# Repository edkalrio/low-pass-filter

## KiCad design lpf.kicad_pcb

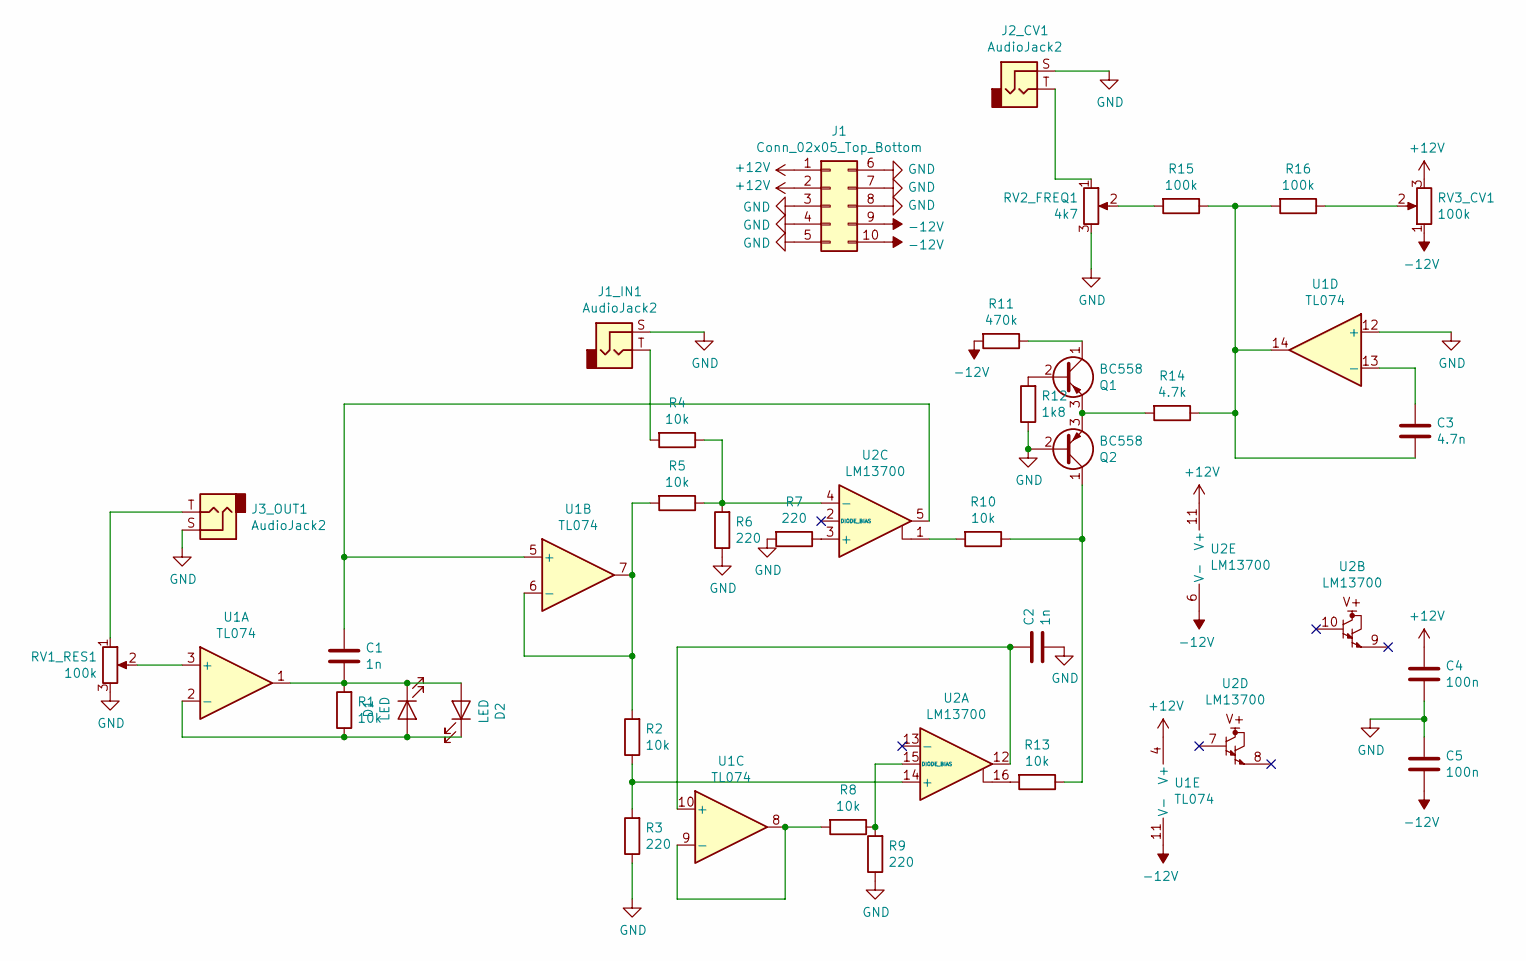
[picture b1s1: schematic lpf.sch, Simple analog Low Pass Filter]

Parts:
C1, C2: 1n; C_Disc_D3.0mm_W1.6mm_P2.50mm
C3: 4.7n; C_Disc_D3.0mm_W1.6mm_P2.50mm
C4, C5: 100n; C_Disc_D3.0mm_W1.6mm_P2.50mm
D1, D2: LED; LED_D3.0mm_Horizontal_O1.27mm_Z2.0mm
J1: Conn_02x05_Top_Bottom; PinHeader_2x05_P2.54mm_Vertical
J1_IN1, J2_CV1, J3_OUT1: AudioJack2; Jack_3.5mm_CUI_SJ1-3533NG_Horizontal_CircularHoles
Q1, Q2: BC558; TO-92_Inline
R1, R2, R4, R5, R8, R10, R13: 10k; R_Axial_DIN0204_L3.6mm_D1.6mm_P5.08mm_Horizontal
R3, R6, R7, R9: 220; R_Axial_DIN0204_L3.6mm_D1.6mm_P5.08mm_Horizontal
R11: 470k; R_Axial_DIN0204_L3.6mm_D1.6mm_P5.08mm_Horizontal
R12: 1k8; R_Axial_DIN0204_L3.6mm_D1.6mm_P5.08mm_Horizontal
R14: 4.7k; R_Axial_DIN0204_L3.6mm_D1.6mm_P5.08mm_Horizontal
R15, R16: 100k; R_Axial_DIN0204_L3.6mm_D1.6mm_P5.08mm_Horizontal
RV1_RES1, RV3_CV1: 100k; Potentiometer_Alps_RK09Y11_Single_Horizontal
RV2_FREQ1: 4k7; Potentiometer_Alps_RK09Y11_Single_Horizontal
U1: TL074; DIP-14_W7.62mm
U2: LM13700; DIP-16_W7.62mm

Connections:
+12V: C4.1, J1.1, J1.2, RV3_CV1.3, U1.4 (V+), U2.11 (V+)
-12V: C5.2, J1.9, J1.10, R11.2, RV3_CV1.1, U1.11 (V-), U2.6 (V-)
GND: C2.2, C4.2, C5.1, J1.3, J1.4, J1.5, J1.6, J1.7, J1.8, J1_IN1.S, J2_CV1.S, J3_OUT1.S, Q2.2 (B), R3.1, R6.1, R7.2, R9.1, R12.1, RV1_RES1.3, RV2_FREQ1.3, U1.12 (+)
unnamed: C1.1, U1.5 (+), U2.5
unnamed: C1.2, D1.1 (K), D2.2 (A), R1.2, U1.1
unnamed: C2.1, U1.10 (+), U2.12
unnamed: C3.1, U1.13 (-)
unnamed: C3.2, R14.1, R15.1, R16.2, U1.14
unnamed: D1.2 (A), D2.1 (K), R1.1, U1.2 (-)
unnamed: J1_IN1.T, R4.2
unnamed: J2_CV1.T, RV2_FREQ1.1
unnamed: J3_OUT1.T, RV1_RES1.1
unnamed: Q1.1 (C), R11.1
unnamed: Q1.2 (B), R12.2
unnamed: Q1.3 (E), Q2.3 (E), R14.2
unnamed: Q2.1 (C), R10.1, R13.1
unnamed: R2.1, R3.2, U2.14 (+)
unnamed: R2.2, R5.2, U1.6 (-), U1.7
unnamed: R4.1, R5.1, R6.2, U2.4 (-)
unnamed: R7.1, U2.3 (+)
unnamed: R8.2, U1.8, U1.9 (-)
unnamed: R10.2, U2.1
unnamed: R13.2, U2.16
unnamed: R15.2, RV2_FREQ1.2
unnamed: R16.1, RV3_CV1.2
unnamed: RV1_RES1.2, U1.3 (+)

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
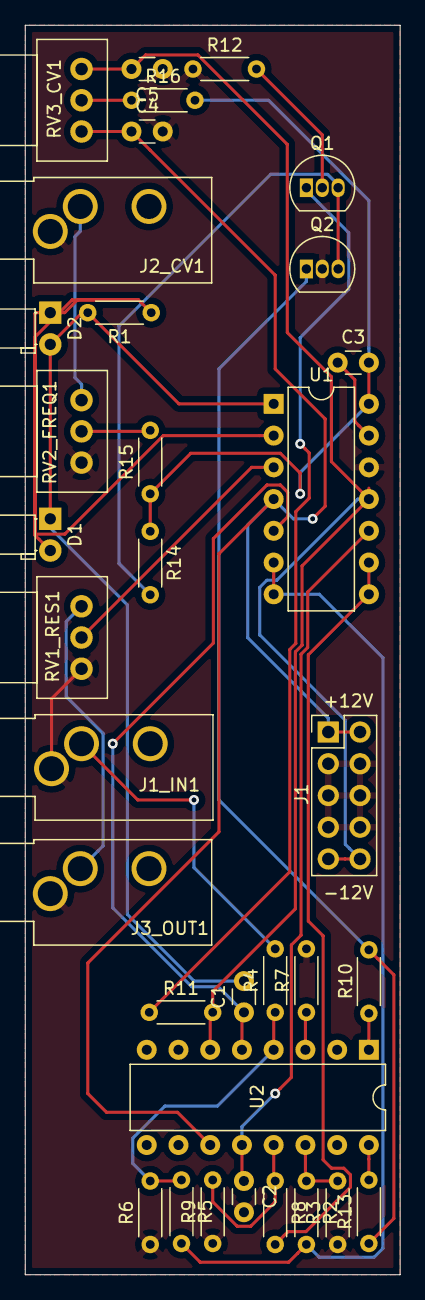
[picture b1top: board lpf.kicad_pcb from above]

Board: 2 copper layers, 30.0 x 100.0 mm, 34 parts (0 on the bottom side), 27 nets.

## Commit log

2019-05-18 I forgot commiting 3 weeks ago :(
